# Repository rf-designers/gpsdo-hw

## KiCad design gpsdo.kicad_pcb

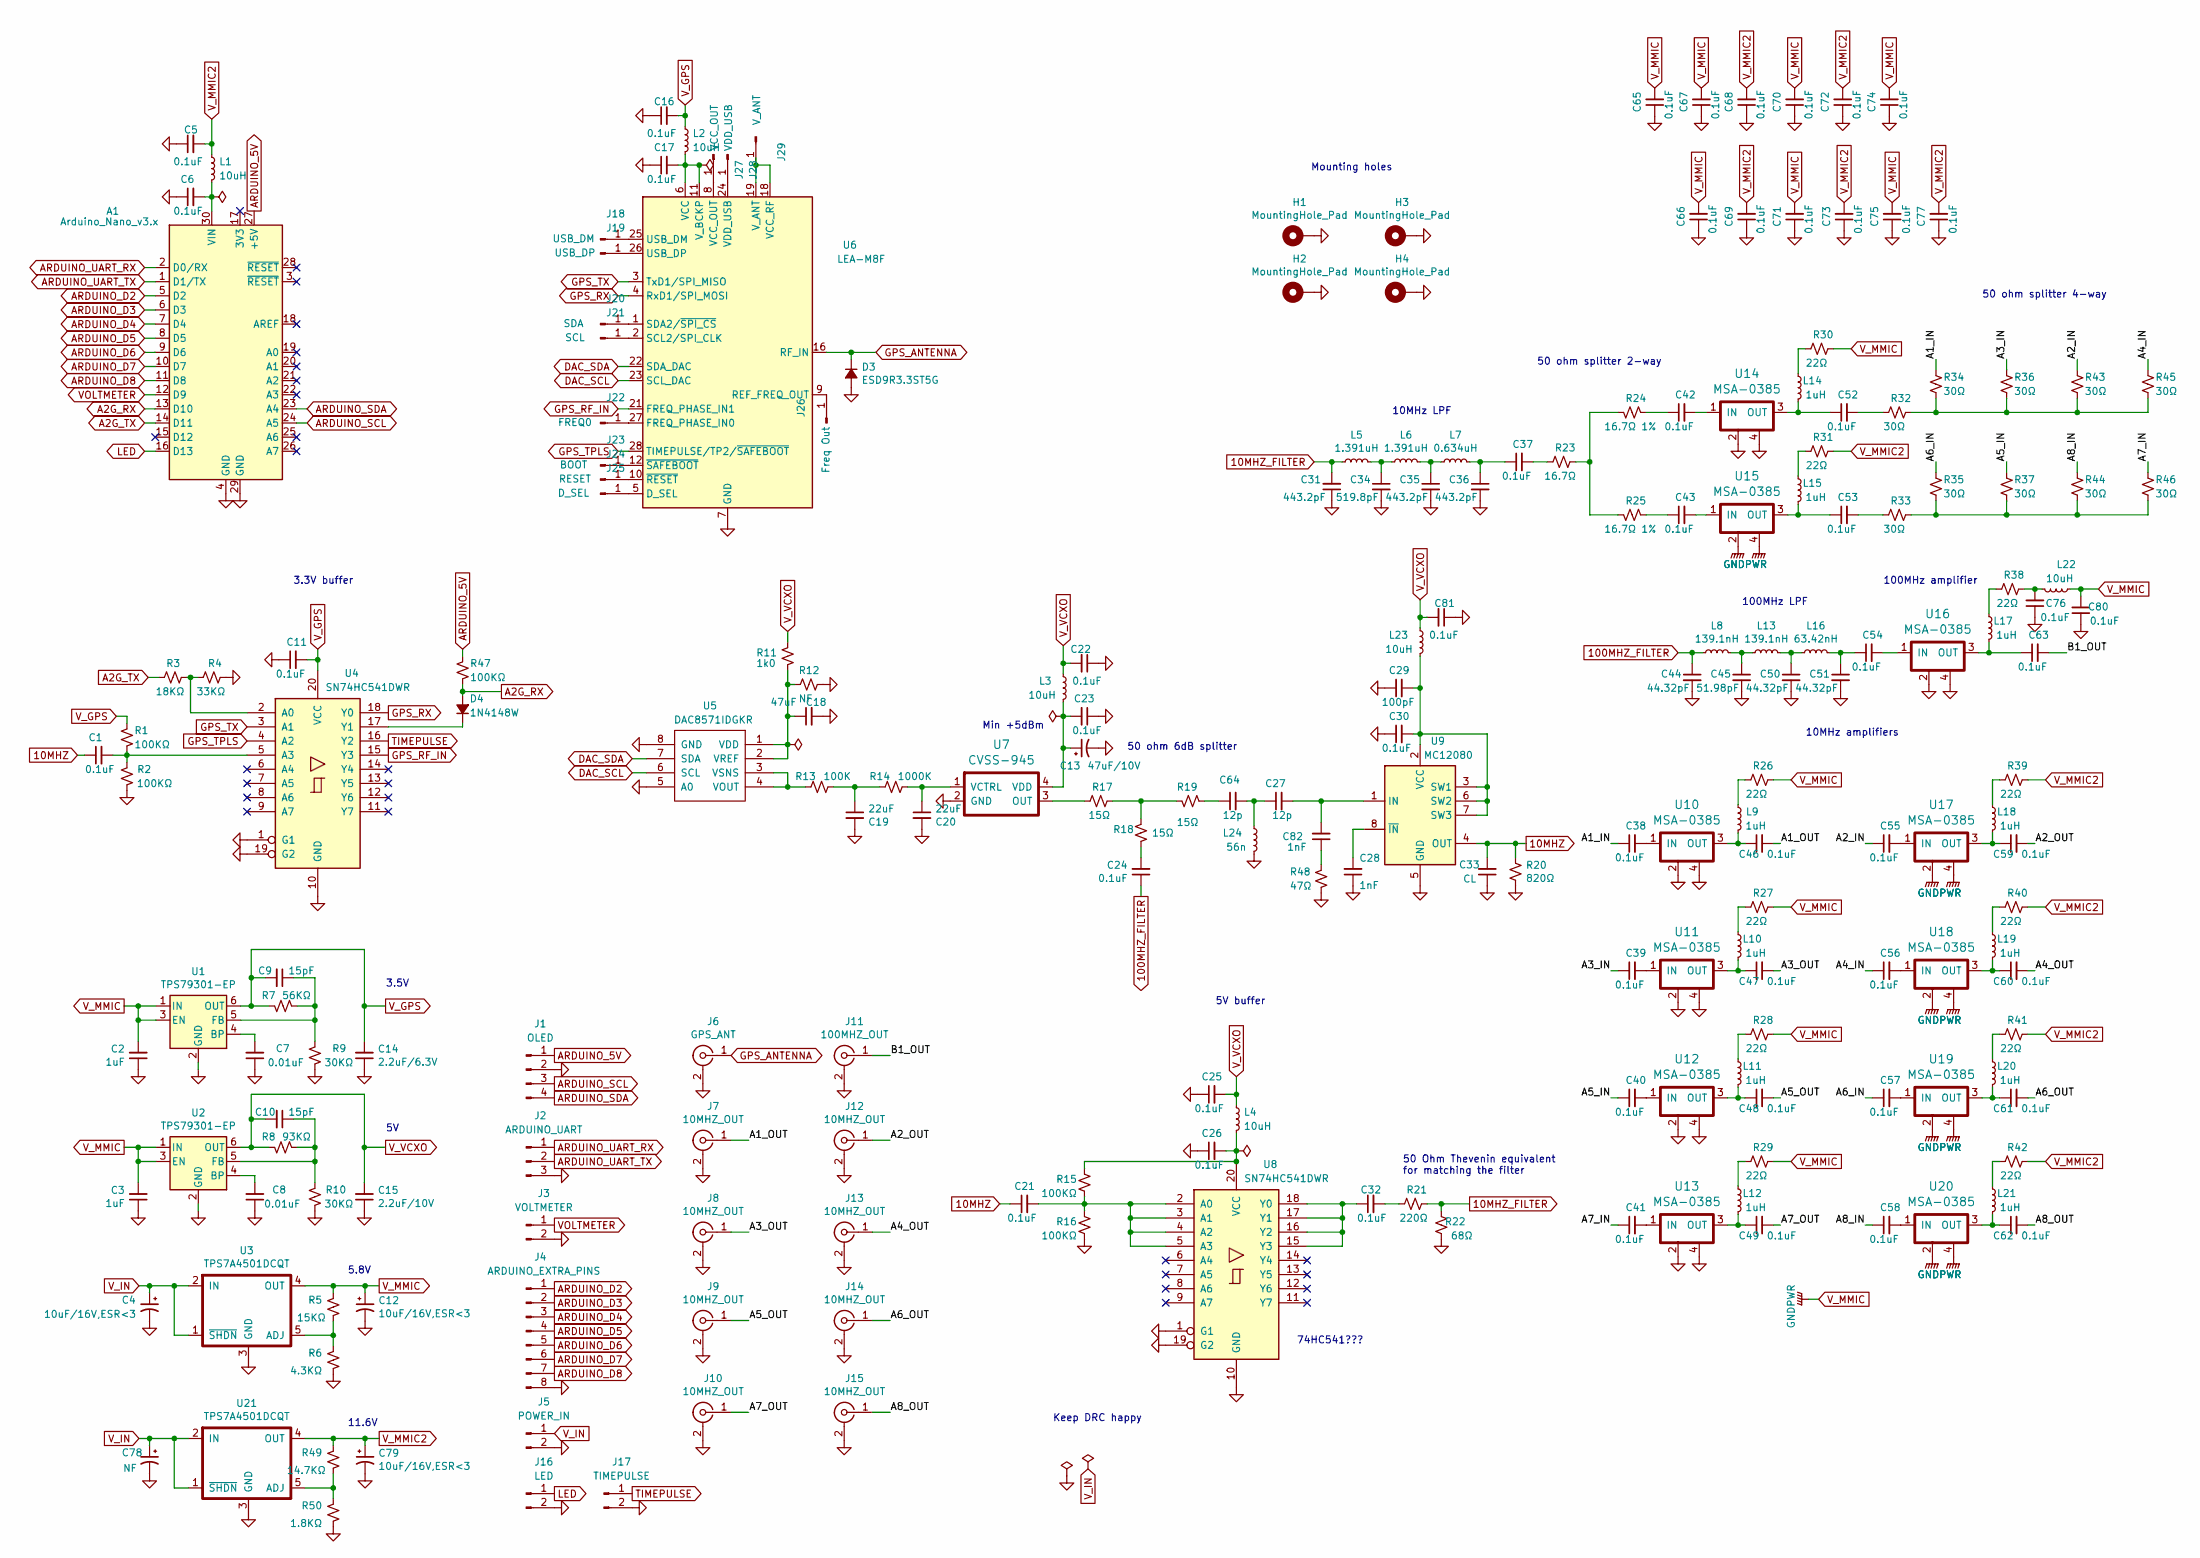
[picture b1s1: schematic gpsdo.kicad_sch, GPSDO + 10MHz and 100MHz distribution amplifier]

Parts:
A1: Arduino_Nano_v3.x; Arduino_Nano
C1, C5, C6, C11, C16, C17, C21, C22, C23, C24, C25, C26, C30, C32, C37, C38, C39, C40, C41, C42, C43, C46, C47, C48, C49, C52, C53, C54, C55, C56, C57, C58, C59, C60, C61, C62, C63, C65, C66, C67, C68, C69, C70, C71, C72, C73, C74, C75, C76, C77, C80, C81: 0.1uF; C_0805_2012Metric_Pad1.18x1.45mm_HandSolder
C2, C3: 1uF; C_0805_2012Metric_Pad1.18x1.45mm_HandSolder
C4, C12, C79: 10uF/16V,ESR<3; C_0805_2012Metric_Pad1.18x1.45mm_HandSolder
C7, C8: 0.01uF; C_0805_2012Metric_Pad1.18x1.45mm_HandSolder
C9, C10: 15pF; C_0805_2012Metric_Pad1.18x1.45mm_HandSolder
C13: 47uF/10V; leaded_elec
C14: 2.2uF/6.3V; C_0805_2012Metric_Pad1.18x1.45mm_HandSolder
C15: 2.2uF/10V; C_0805_2012Metric_Pad1.18x1.45mm_HandSolder
C18: 47uF; leaded_elec
C19, C20: 22uF; leaded_elec
C27, C64: 12p; C_0805_2012Metric_Pad1.18x1.45mm_HandSolder
C28, C82: 1nF; C_0805_2012Metric_Pad1.18x1.45mm_HandSolder
C29: 100pF; C_0805_2012Metric_Pad1.18x1.45mm_HandSolder
C31, C35, C36: 443.2pF; C_0805_2012Metric_Pad1.18x1.45mm_HandSolder
C33: CL; C_0805_2012Metric_Pad1.18x1.45mm_HandSolder
C34: 519.8pF; C_0805_2012Metric_Pad1.18x1.45mm_HandSolder
C44, C50, C51: 44.32pF; C_0805_2012Metric_Pad1.18x1.45mm_HandSolder
C45: 51.98pF; C_0805_2012Metric_Pad1.18x1.45mm_HandSolder
C78: NF; C_0805_2012Metric_Pad1.18x1.45mm_HandSolder
D3: ESD9R3.3ST5G; D_0402_1005Metric
D4: 1N4148W; D_SOD-123
H1, H2, H3, H4: MountingHole_Pad; MountingHole_3.2mm_M3_DIN965_Pad
J1: OLED; PinHeader_1x04_P2.54mm_Vertical
J2: ARDUINO_UART; PinHeader_1x03_P2.54mm_Vertical
J3: VOLTMETER; PinHeader_1x02_P2.54mm_Vertical
J4: ARDUINO_EXTRA_PINS; PinHeader_1x08_P2.54mm_Vertical
J5: POWER_IN; PinHeader_1x02_P2.54mm_Vertical
J6: GPS_ANT; SMA_Amphenol_132134_Vertical
J7, J8, J9, J10, J12, J13, J14, J15: 10MHZ_OUT; SMA_Amphenol_132134_Vertical
J11: 100MHZ_OUT; SMA_Amphenol_132134_Vertical
J16: LED; PinHeader_1x02_P2.54mm_Vertical
J17: TIMEPULSE; PinHeader_1x02_P2.54mm_Vertical
J18: USB_DM; Single_SMD_Pad
J19: USB_DP; Single_SMD_Pad
J20: SDA; Single_SMD_Pad
J21: SCL; Single_SMD_Pad
J22: FREQ0; Single_SMD_Pad
J23: BOOT; Single_SMD_Pad
J24: RESET; Single_SMD_Pad
J25: D_SEL; Single_SMD_Pad
J26: Freq Out; Single_SMD_Pad
J27: VCC_OUT; Single_SMD_Pad
J28: VDD_USB; Single_SMD_Pad
J29: V_ANT; Single_SMD_Pad
L1, L2, L3, L4, L22, L23: 10uH; L_0805_2012Metric_Pad1.15x1.40mm_HandSolder
L5, L6: 1.391uH; L_0805_2012Metric_Pad1.15x1.40mm_HandSolder
L7: 0.634uH; L_0805_2012Metric_Pad1.15x1.40mm_HandSolder
L8, L13: 139.1nH; L_0805_2012Metric_Pad1.15x1.40mm_HandSolder
L9, L10, L11, L12, L14, L15, L17, L18, L19, L20, L21: 1uH; L_0805_2012Metric_Pad1.15x1.40mm_HandSolder
L16: 63.42nH; L_0805_2012Metric_Pad1.15x1.40mm_HandSolder
L24: 56n; L_0805_2012Metric_Pad1.15x1.40mm_HandSolder
R1, R2, R15, R16, R47: 100KΩ; R_0805_2012Metric_Pad1.20x1.40mm_HandSolder
R3: 18KΩ; R_0805_2012Metric_Pad1.20x1.40mm_HandSolder
R4: 33KΩ; R_0805_2012Metric_Pad1.20x1.40mm_HandSolder
R5: 15KΩ; R_0805_2012Metric_Pad1.20x1.40mm_HandSolder
R6: 4.3KΩ; R_0805_2012Metric_Pad1.20x1.40mm_HandSolder
R7: 56KΩ; R_0805_2012Metric_Pad1.20x1.40mm_HandSolder
R8: 93KΩ; R_0805_2012Metric_Pad1.20x1.40mm_HandSolder
R9, R10: 30KΩ; R_0805_2012Metric_Pad1.20x1.40mm_HandSolder
R11: 1k0; R_0805_2012Metric_Pad1.20x1.40mm_HandSolder
R12: NF; R_0805_2012Metric_Pad1.20x1.40mm_HandSolder
R13: 100K; R_0805_2012Metric_Pad1.20x1.40mm_HandSolder
R14: 1000K; R_0805_2012Metric_Pad1.20x1.40mm_HandSolder
R17, R18, R19: 15Ω; R_0805_2012Metric_Pad1.20x1.40mm_HandSolder
R20: 820Ω; R_0805_2012Metric_Pad1.20x1.40mm_HandSolder
R21: 220Ω; R_0805_2012Metric_Pad1.20x1.40mm_HandSolder
R22: 68Ω; R_0805_2012Metric_Pad1.20x1.40mm_HandSolder
R23: 16.7Ω; R_0805_2012Metric_Pad1.20x1.40mm_HandSolder
R24, R25: 16.7Ω 1%; R_0805_2012Metric_Pad1.20x1.40mm_HandSolder
R26, R27, R28, R29, R30, R31, R38, R39, R40, R41, R42: 22Ω; R_0805_2012Metric_Pad1.20x1.40mm_HandSolder
R32, R33, R34, R35, R36, R37, R43, R44, R45, R46: 30Ω; R_0805_2012Metric_Pad1.20x1.40mm_HandSolder
R48: 47Ω; R_0805_2012Metric_Pad1.20x1.40mm_HandSolder
R49: 14.7KΩ; R_0805_2012Metric_Pad1.20x1.40mm_HandSolder
R50: 1.8KΩ; R_0805_2012Metric_Pad1.20x1.40mm_HandSolder
U1, U2: TPS79301-EP; SOT-23-6
U3, U21: TPS7A4501DCQT; SOT-223-6
U4, U8: SN74HC541DWR; SOIC-20W_7.5x12.8mm_P1.27mm
U5: DAC8571IDGKR; VSSOP-8_3.0x3.0mm_P0.65mm
U6: LEA-M8F; ublox_LEA
U7: CVSS-945
U9: MC12080; SOIC-8_3.9x4.9mm_P1.27mm
U10, U11, U12, U13, U14, U15, U16, U17, U18, U19, U20: MSA-0385; PL262

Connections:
10MHZ: C1.1, C21.1, C33.2, R20.1, U9.4 (OUT)
10MHZ_FILTER: C31.2, L5.1, R21.1, R22.2
100MHZ_FILTER: C24.1, C44.1, L8.1
/A1_IN: C38.1, R34.1
/A1_OUT: C46.2, J7.1 (In)
/A2_IN: C55.1, R43.1
/A2_OUT: C59.2, J12.1 (In)
/A3_IN: C39.1, R36.1
/A3_OUT: C47.2, J8.1 (In)
/A4_IN: C56.1, R45.1
/A4_OUT: C60.2, J13.1 (In)
/A5_IN: C40.1, R37.1
/A5_OUT: C48.2, J9.1 (In)
/A6_IN: C57.1, R35.1
/A6_OUT: C61.2, J14.1 (In)
/A7_IN: C41.1, R46.1
/A7_OUT: C49.2, J10.1 (In)
/A8_IN: C58.1, R44.1
/A8_OUT: C62.2, J15.1 (In)
/B1_OUT: C63.2, J11.1 (In)
A2G_RX: A1.13 (D10), D4.2 (A), R47.1
A2G_TX: A1.14 (D11), R3.2
ARDUINO_5V: A1.27 (+5V), J1.1, R47.2
ARDUINO_D2: A1.5 (D2), J4.1
ARDUINO_D3: A1.6 (D3), J4.2
ARDUINO_D4: A1.7 (D4), J4.3
ARDUINO_D5: A1.8 (D5), J4.4
ARDUINO_D6: A1.9 (D6), J4.5
ARDUINO_D7: A1.10 (D7), J4.6
ARDUINO_D8: A1.11 (D8), J4.7
ARDUINO_SCL: A1.24 (A5), J1.3
ARDUINO_SDA: A1.23 (A4), J1.4
ARDUINO_UART_RX: A1.2 (D0/RX), J2.1
ARDUINO_UART_TX: A1.1 (D1/TX), J2.2
DAC_SCL: U5.6 (SCL), U6.23 (SCL_DAC)
DAC_SDA: U5.7 (SDA), U6.22 (SDA_DAC)
GND: A1.4 (GND), A1.29 (GND), C2.1, C3.1, C4.2, C5.1, C6.1, C7.1, C8.1, C11.1, C12.2, C13.2, C14.1, C15.1, C16.1, C17.1, C18.2, C19.2, C20.2, C22.1, C23.1, C25.1, C26.1, C28.1, C29.1, C30.1, C31.1, C33.1, C34.2, C35.2, C36.2, C44.2, C45.2, C50.2, C51.2, C65.1, C66.1, C67.1, C68.1, C69.1, C70.1, C71.1, C72.1, C73.1, C74.1, C75.1, C76.1, C77.1, C78.2, C79.2, C80.1, C81.1, D3.2 (A), H1.1, H2.1, H3.1, H4.1, J1.2, J2.3, J3.2, J4.8, J5.2, J6.2 (Ext), J7.2 (Ext), J8.2 (Ext), J9.2 (Ext), J10.2 (Ext), J11.2 (Ext), J12.2 (Ext), J13.2 (Ext), J14.2 (Ext), J15.2 (Ext), J16.2, J17.2, L24.2, R2.2, R4.2, R6.2, R9.2, R10.2, R12.1, R16.1, R20.2, R22.1, R48.1, R50.2, U1.2 (GND), U2.2 (GND), U3.3 (GND), U4.1 (G1), U4.10 (GND), U4.19 (G2), U5.5 (A0), U5.8 (GND), U6.7 (GND), U6.13 (GND), U6.14 (GND), U6.15 (GND), U6.17 (GND), U7.2 (GND), U8.1 (G1), U8.10 (GND), U8.19 (G2), U9.5 (GND), U10.2, U10.4, U11.2, U11.4, U12.2, U12.4, U13.2, U13.4, U14.2, U14.4, U16.2, U16.4, U21.3 (GND)
GPS_ANTENNA: D3.1 (K), J6.1 (In), U6.16 (RF_IN)
GPS_RF_IN: U4.15 (Y3), U6.21 (FREQ_PHASE_IN1)
GPS_RX: U4.18 (Y0), U6.4 (RxD1/SPI_MOSI)
GPS_TPLS: U4.4 (A2), U6.28 (TIMEPULSE/TP2/~SAFEBOOT)
GPS_TX: U4.3 (A1), U6.3 (TxD1/SPI_MISO)
LED: A1.16 (D13), J16.1
unnamed: A1.30 (VIN), C6.2, L1.2
unnamed: C1.2, R1.1, R2.1, U4.5 (A3)
unnamed: C7.2, U1.4 (BP)
unnamed: C8.2, U2.4 (BP)
unnamed: C9.1, R7.2, R9.1, U1.5 (FB)
unnamed: C10.1, R8.2, R10.1, U2.5 (FB)
unnamed: C13.1, C23.2, L3.2, U7.4 (VDD)
unnamed: C17.2, L2.2, U6.6 (VCC), U6.11 (V_BCKP)
unnamed: C18.1, R11.1, R12.2, U5.1 (VDD), U5.2 (VREF)
unnamed: C19.1, R13.1, R14.2
unnamed: C20.1, R14.1, U7.1 (VCTRL)
unnamed: C21.2, R15.1, R16.2, U8.2 (A0), U8.3 (A1), U8.4 (A2), U8.5 (A3)
unnamed: C24.2, R18.1
unnamed: C26.2, L4.2, R15.2, U8.20 (VCC)
unnamed: C27.1, C64.2, L24.1
unnamed: C27.2, C82.2, U9.1 (IN)
unnamed: C28.2, U9.8 (~IN)
unnamed: C29.2, C30.2, L23.2, U9.2 (VCC), U9.3 (SW1), U9.6 (SW2), U9.7 (SW3)
unnamed: C32.1, U8.15 (Y3), U8.16 (Y2), U8.17 (Y1), U8.18 (Y0)
unnamed: C32.2, R21.2
unnamed: C34.1, L5.2, L6.1
unnamed: C35.1, L6.2, L7.1
unnamed: C36.1, C37.1, L7.2
unnamed: C37.2, R23.2
unnamed: C38.2, U10.1 (IN)
unnamed: C39.2, U11.1 (IN)
unnamed: C40.2, U12.1 (IN)
unnamed: C41.2, U13.1 (IN)
unnamed: C42.1, R24.1
unnamed: C42.2, U14.1 (IN)
unnamed: C43.1, R25.1
unnamed: C43.2, U15.1 (IN)
unnamed: C45.1, L8.2, L13.1
unnamed: C46.1, L9.2, U10.3 (OUT)
unnamed: C47.1, L10.2, U11.3 (OUT)
unnamed: C48.1, L11.2, U12.3 (OUT)
unnamed: C49.1, L12.2, U13.3 (OUT)
unnamed: C50.1, L13.2, L16.1
unnamed: C51.1, C54.1, L16.2
unnamed: C52.1, L14.2, U14.3 (OUT)
unnamed: C52.2, R32.2
unnamed: C53.1, L15.2, U15.3 (OUT)
unnamed: C53.2, R33.2
unnamed: C54.2, U16.1 (IN)
unnamed: C55.2, U17.1 (IN)
unnamed: C56.2, U18.1 (IN)
unnamed: C57.2, U19.1 (IN)
unnamed: C58.2, U20.1 (IN)
unnamed: C59.1, L18.2, U17.3 (OUT)
unnamed: C60.1, L19.2, U18.3 (OUT)
unnamed: C61.1, L20.2, U19.3 (OUT)
unnamed: C62.1, L21.2, U20.3 (OUT)
unnamed: C63.1, L17.2, U16.3 (OUT)
unnamed: C64.1, R19.1
unnamed: D4.1 (K), U4.17 (Y1)
unnamed: J18.1, U6.25 (USB_DM)
unnamed: J19.1, U6.26 (USB_DP)
unnamed: J20.1, U6.1 (SDA2/~SPI_CS)
unnamed: J21.1, U6.2 (SCL2/SPI_CLK)
unnamed: J22.1, U6.27 (FREQ_PHASE_IN0)
unnamed: J23.1, U6.12 (~SAFEBOOT)
unnamed: J24.1, U6.10 (~RESET)
unnamed: J25.1, U6.5 (D_SEL)
unnamed: J26.1, U6.9 (REF_FREQ_OUT)
unnamed: J27.1, U6.8 (VCC_OUT)
unnamed: J28.1, U6.24 (VDD_USB)
unnamed: J29.1, U6.18 (VCC_RF), U6.19 (V_ANT)
unnamed: L9.1, R26.2
unnamed: L10.1, R27.2
unnamed: L11.1, R28.2
unnamed: L12.1, R29.2
unnamed: L14.1, R30.2
unnamed: L15.1, R31.2
unnamed: L17.1, R38.2
unnamed: L18.1, R39.2
unnamed: L19.1, R40.2
unnamed: L20.1, R41.2
unnamed: L21.1, R42.2
unnamed: R3.1, R4.1, U4.2 (A0)
unnamed: R5.2, R6.1, U3.5 (ADJ)
unnamed: R13.2, U5.3 (VSNS), U5.4 (VOUT)
unnamed: R17.1, R18.2, R19.2
unnamed: R17.2, U7.3 (OUT)
unnamed: R23.1, R24.2, R25.2
unnamed: R32.1, R34.2, R36.2, R43.2, R45.2
unnamed: R33.1, R35.2, R37.2, R44.2, R46.2
unnamed: C76.2, L22.2, R38.1
unnamed: C82.1, R48.2
unnamed: R49.2, R50.1, U21.5 (ADJ)
TIMEPULSE: J17.1, U4.16 (Y2)
VOLTMETER: A1.12 (D9), J3.1
V_GPS: C9.2, C11.2, C14.2, C16.2, L2.1, R1.2, R7.1, U1.6 (OUT), U4.20 (VCC)
V_IN: C4.1, C78.1, J5.1, U3.1 (~SHDN), U3.2 (IN), U21.1 (~SHDN), U21.2 (IN)
V_MMIC: C2.2, C3.2, C12.1, C65.2, C66.2, C67.2, C70.2, C71.2, C74.2, C75.2, C80.2, L22.1, R5.1, R26.1, R27.1, R28.1, R29.1, R30.1, U1.1 (IN), U1.3 (EN), U2.1 (IN), U2.3 (EN), U3.4 (OUT), U15.2, U15.4, U17.2, U17.4, U18.2, U18.4, U19.2, U19.4, U20.2, U20.4
V_MMIC2: C5.2, C68.2, C69.2, C72.2, C73.2, C77.2, C79.1, L1.1, R31.1, R39.1, R40.1, R41.1, R42.1, R49.1, U21.4 (OUT)
V_VCXO: C10.2, C15.2, C22.2, C25.2, C81.2, L3.1, L4.1, L23.1, R8.1, R11.2, U2.6 (OUT)

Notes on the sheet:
3.3V buffer
5.8V
11.6V
3.5V
Min +5dBm
Keep DRC happy
50 ohm 6dB splitter
5V buffer
74HC541???
Mounting holes
10MHz LPF
50 Ohm Thevenin equivalent for matching the filter
50 ohm splitter 2-way
100MHz LPF
10MHz amplifiers
100MHz amplifier
50 ohm splitter 4-way

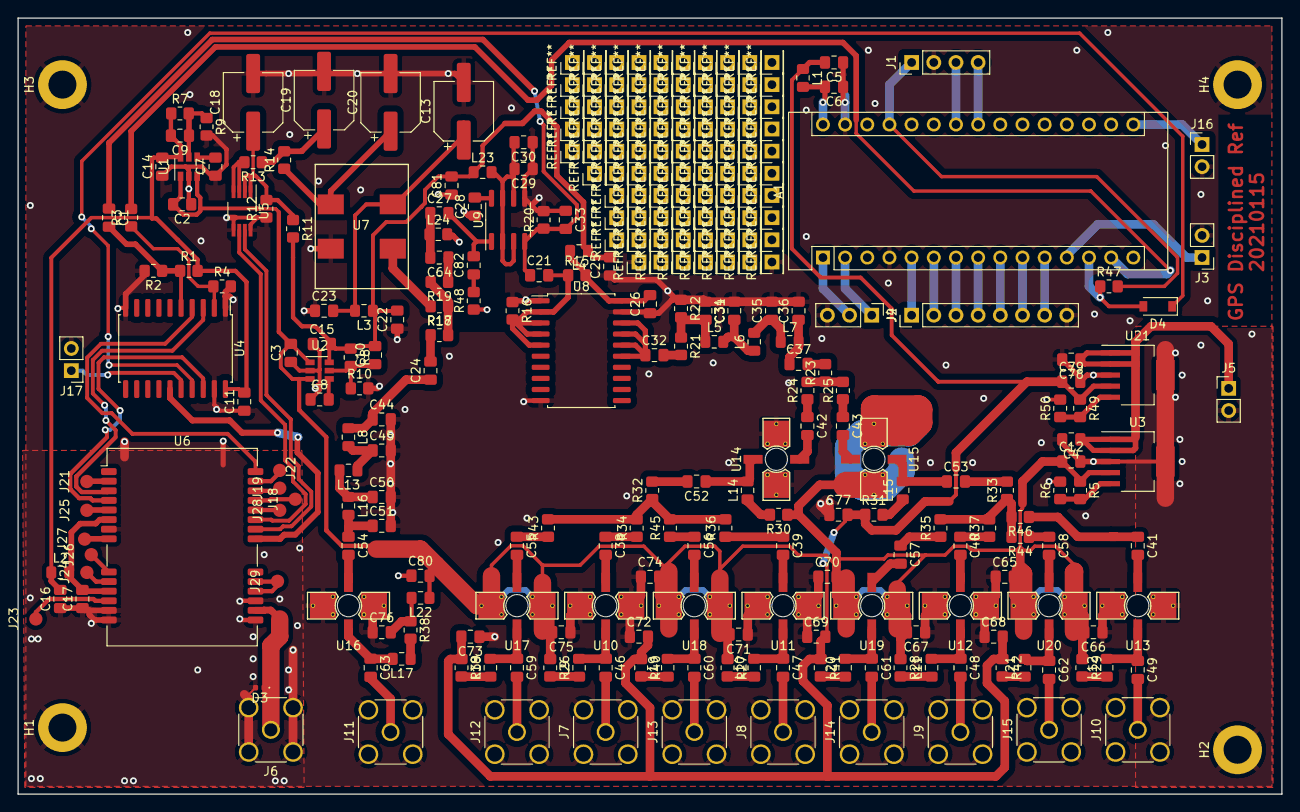
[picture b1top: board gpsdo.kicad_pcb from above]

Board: 2 copper layers, 144.8 x 88.9 mm, 212 parts (0 on the bottom side), 138 nets.

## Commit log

2019-08-25 A first working version
2019-08-28 Implemented fixes following Frederic's review
2019-08-30 Reworked V_MMIC to accomodate TPS7A4501DCQT and made DRC pass
2020-12-27 firstModifications
2021-01-07 Made ERC pass and updated footprint assignments
2021-01-08 Reworked V_MMIC resistors for 5.5V and added V_MMIC2 for 11.13V
2021-01-12 checked
2021-01-12 Changed U8 buffer to 74HC541
2021-01-12 Added GPS pins and mounting holes
2021-01-12 Updated U4 to 541
2021-01-13 first_layout
2021-01-13 placement_almost_done
2021-01-13 changed_schematic
2021-01-14 temp
2021-01-14 Updated footprints
2021-01-14 progress
2021-01-15 final
2021-01-15 Dragged vias underneath U4 and rotated the layout
2021-01-15 moved_track
2021-01-15 moved_track_again
2021-01-15 GND_plane
2021-01-15 Updated symbols background
2021-01-15 Added auxilliary axis origin
2021-01-15 Cosmetics
2021-02-12 shematic_10MHz
2021-02-12 solved_10MHz_issues
2021-02-12 Updated schematic references
